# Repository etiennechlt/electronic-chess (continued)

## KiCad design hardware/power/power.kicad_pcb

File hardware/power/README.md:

# Carte puissance : pack 3S, charge, protection, jauge

Générée par `tools/boardgen` (module `power`). 100 x 60 mm, 2 couches,
plan de masse en face arrière. Elle gère trois cellules plates 1S 5 Ah.

- **Entrée** : 20 V depuis un module déclencheur USB-C PD du commerce
  (connecteur JST XH 2 broches), TVS SMBJ24A, sens de courant d'entrée
  10 mohms, deux P-FET AO3401A dos à dos (drain commun) que la sortie
  ACDRV, active bas, pilote.
- **Chargeur** : BQ24610, buck synchrone à deux AO3400A, self 10 µH,
  sens de courant 50 mohms (1 A = 50 mV), régulation 12,6 V par
  diviseur sur VFB, courant de charge 1 A (ISET1 à 0,995 V), précharge
  et fin de charge 0,2 A (ISET2 à 0,101 V), limite d'entrée 2,5 A
  (ACSET à 0,499 V), fenêtre de température 0 à 45 °C par le réseau
  5,23 k / 30,1 k de la fiche sur une CTN 10 k, sorties STAT et PG
  tirées au 3,3 V de l'AFE. Pas de chemin d'alimentation : le système
  tourne sur le pack, BATDRV reste libre.
- **Protection** : BQ76920 (AFE 3 à 5S) avec ses filtres 1 k / 100 nF
  par cellule, deux FET AO3400A en bas côté dans le retour du pack (DSG
  source côté cellules après la résistance de mesure, CHG source sur
  PACK-), sens 5 mohms, CTN, I2C vers le cerveau, sortie ALERT.
- **Jauge** : INA219 sur un shunt 10 mohms côté haut, même bus I2C.
- **Sorties** : fusible 2 A, embase pour un interrupteur, bouton de
  réveil (PWR_KEY), liaison 2 x 4 vers le cerveau, connecteur cellules
  JST XH 4 broches (B-, B1, B2, B+).

Les valeurs d'ISET, d'ACSET et du diviseur de tension suivent
l'application type du BQ24610, revues dans la
[note 14](../../docs/notes/14-revue-des-cartes.md) ; les formules
(ICHG = V(ISET1) / 20 RSR, IPRE = ITERM = V(ISET2) / 10 RSR) et la
plage admise de V(ISET2) restent à confirmer sur la fiche. Points
ouverts : la CTN de charge est sur la carte alors que le yaml la veut
sur le pack (deux broches de plus au connecteur cellules), et le cerveau
ne doit jamais ouvrir DSG par I2C (rien ne le refermerait).

```bash
PYTHONPATH=tools .venv/bin/python -m boardgen build power --render docs/images/power.png
```

## Résultat du build

Généré par `python -m boardgen build power` :

| Composants | Segments | Vias | Nets fermés | Nets ouverts | Défauts d'isolement |
|---|---|---|---|---|---|
| 82 | 429 | 158 | 42 | 10 | 0 |

Nets à finir dans pcbnew (le routeur les a laissés ouverts) :
- REGN: 2 pad(s) left open (usable start cells 28, goal cells 72)
- TS1: 2 pad(s) left open (usable start cells 43, goal cells 63)
- SCL: 4 pad(s) left open (usable start cells 34, goal cells 314)
- SDA: 4 pad(s) left open (usable start cells 34, goal cells 318)
- 3V3_BMS: 1 pad(s) left open (usable start cells 534, goal cells 34)
- SRN: 1 pad(s) left open (usable start cells 163, goal cells 84)
- SRP: 1 pad(s) left open (usable start cells 642, goal cells 84)
- CELL3: 6 pad(s) left open (usable start cells 30, goal cells 483)
- PACK+: 1 pad(s) left open (usable start cells 313, goal cells 100)
- BAT-: 16 pad(s) left open (usable start cells 39, goal cells 969)

DRC KiCad 7 (`tools/drc.py`, zones remplies) : 307 signalements, 69 éléments non connectés (les nets ouverts ci-dessus), erreurs restantes : aucune ; avertissements sans effet sur la fabrication : silk_overlap 121, lib_footprint_issues 82, via_dangling 56, silk_over_copper 36, track_dangling 12. Le contrôle d'isolement exact du générateur ne signale aucun défaut. Les vias d'éventail des boîtiers fins font 0,45 mm (perçage 0,2 mm), dans les capacités standard de JLCPCB, à confirmer sur le devis.

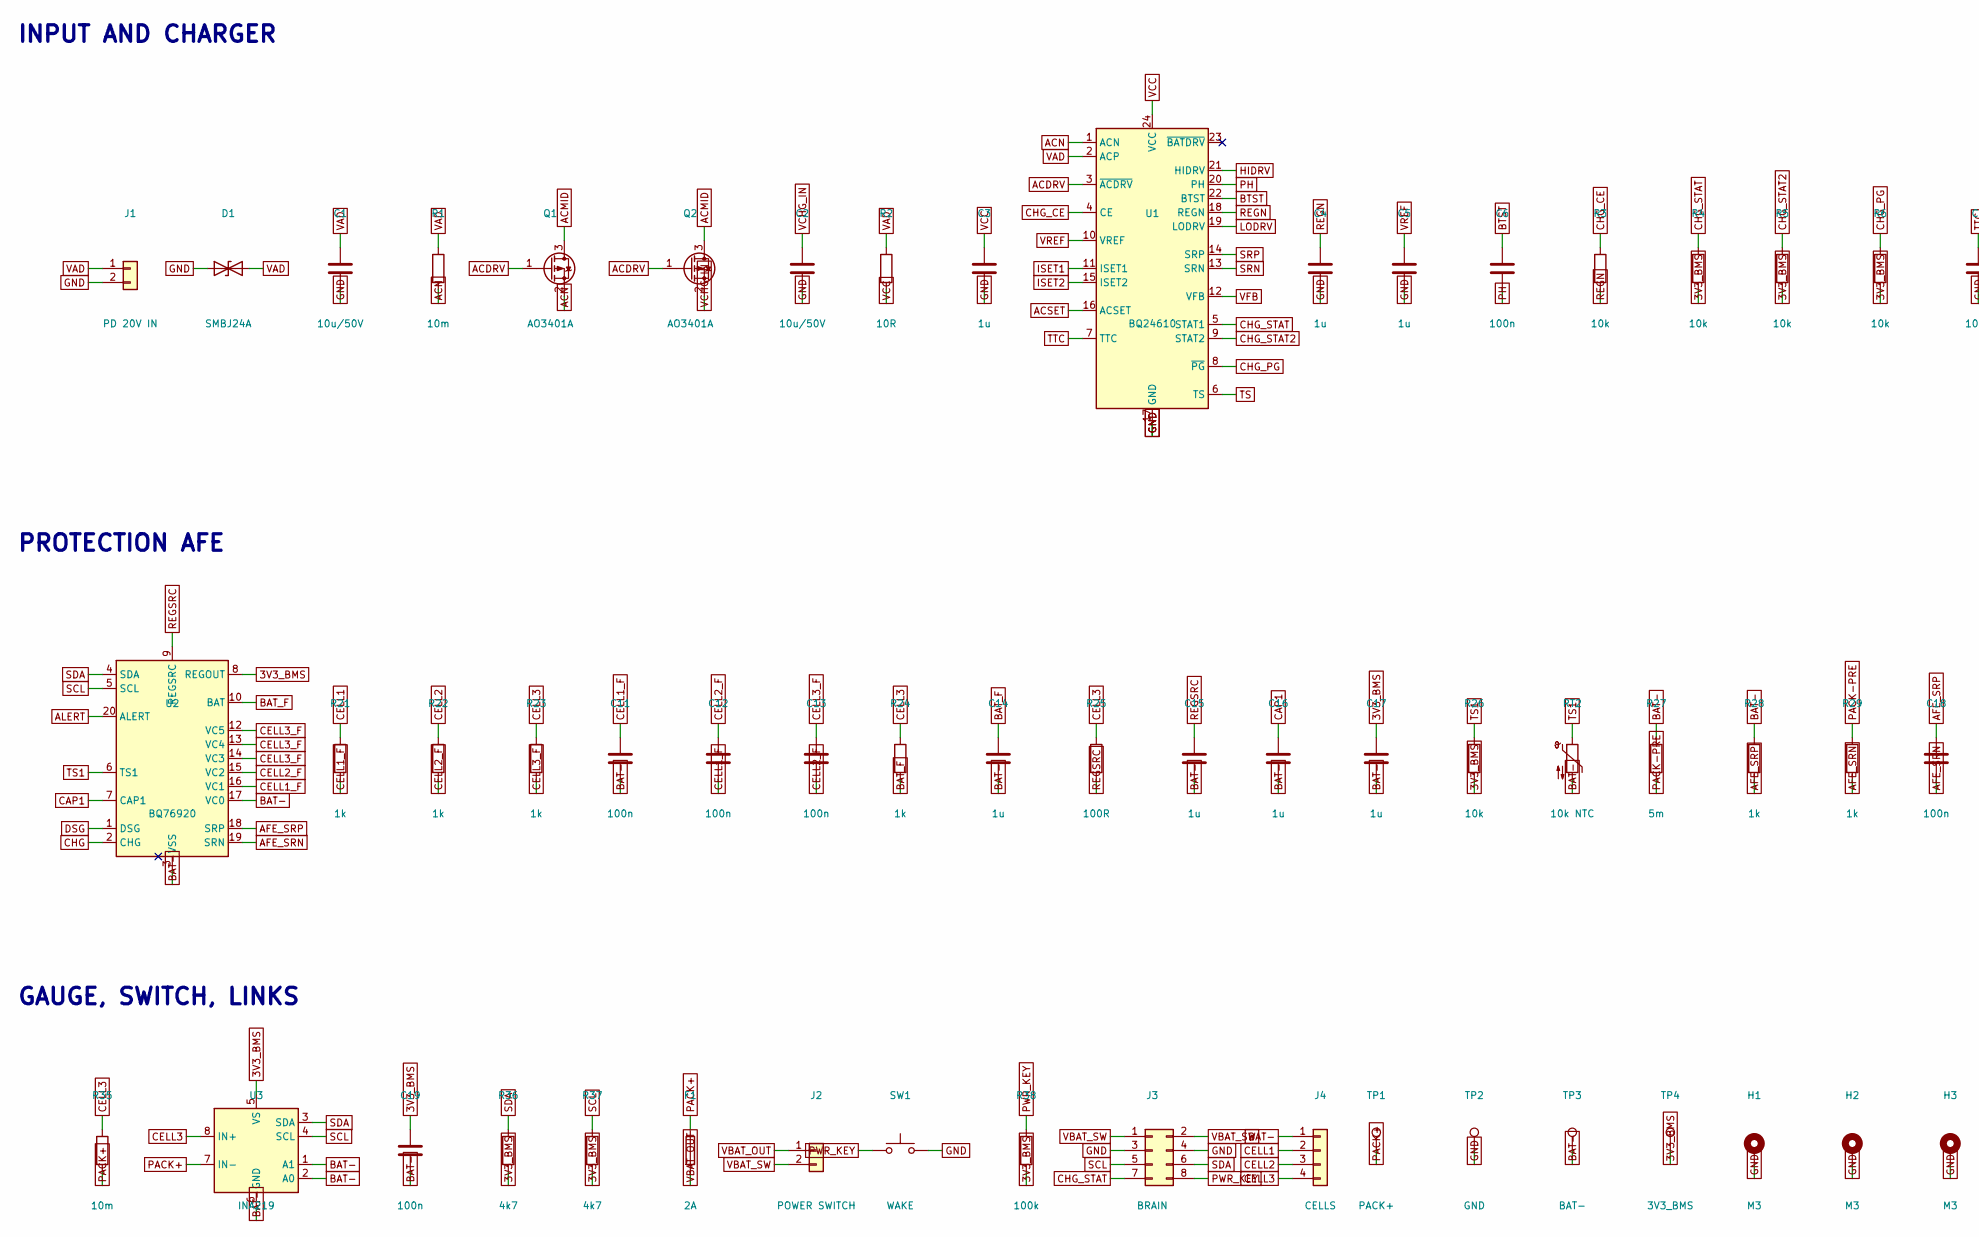
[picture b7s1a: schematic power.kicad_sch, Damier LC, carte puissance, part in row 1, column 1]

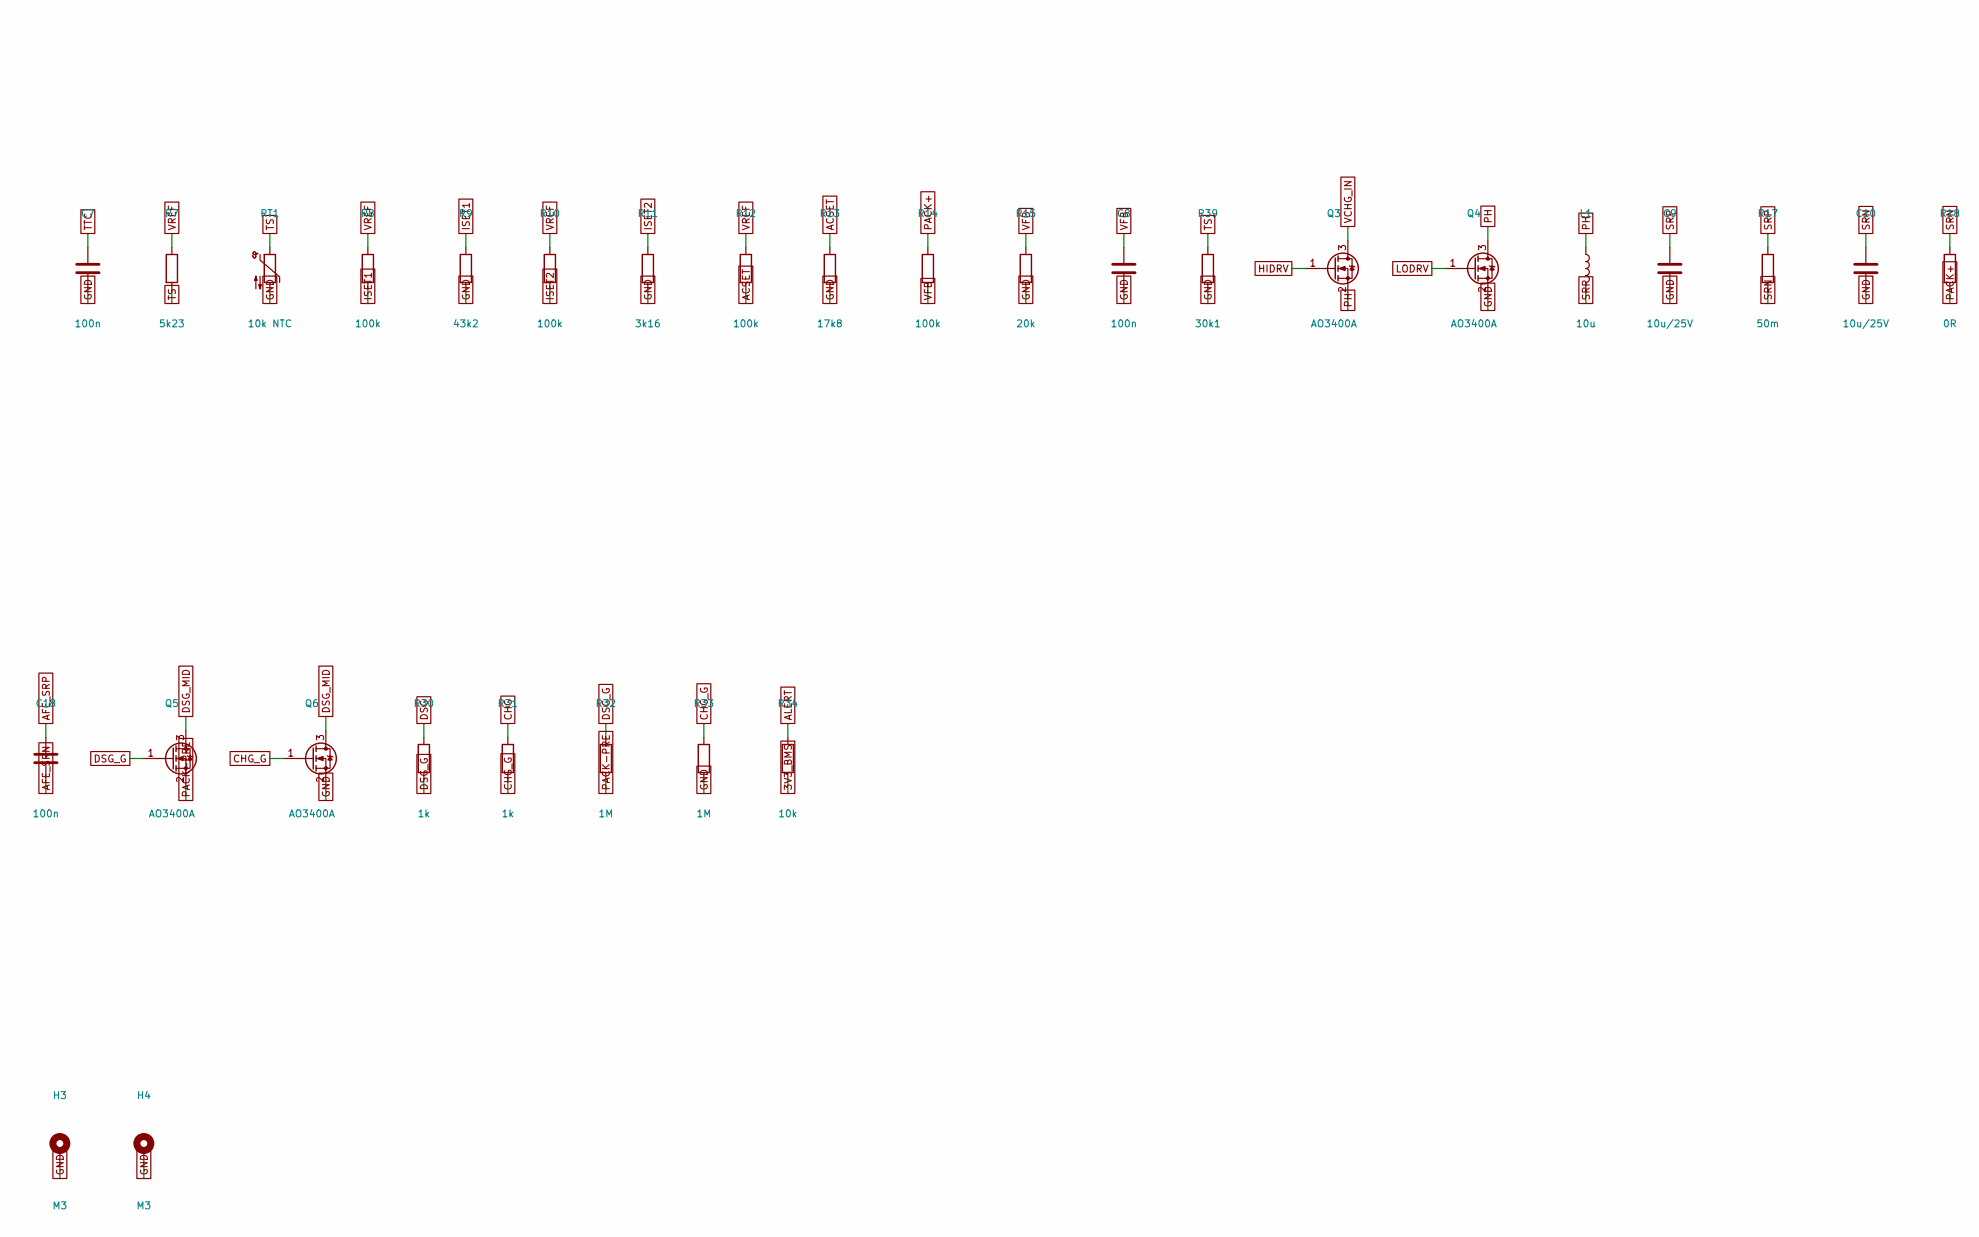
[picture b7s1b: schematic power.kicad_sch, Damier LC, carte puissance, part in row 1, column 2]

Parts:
C1, C2: 10u/50V; C_1206_3216Metric
C3, C4, C5, C14, C15, C16, C17: 1u; C_0603_1608Metric
C6, C7, C8, C11, C12, C13, C18, C19: 100n; C_0603_1608Metric
C9, C10: 10u/25V; C_1206_3216Metric
D1: SMBJ24A; D_SMB; MPN SMBJ24A; LCSC C113966
F1: 2A; Fuse_1206_3216Metric
H1, H2, H3, H4: M3; MountingHole_3.2mm_M3_Pad
J1: PD 20V IN; JST_XH_B2B-XH-A_1x02_P2.50mm_Vertical
J2: POWER SWITCH; JST_XH_B2B-XH-A_1x02_P2.50mm_Vertical
J3: BRAIN; PinHeader_2x04_P2.54mm_Vertical
J4: CELLS; JST_XH_B4B-XH-A_1x04_P2.50mm_Vertical
L1: 10u; L_Bourns_SRN6045TA; MPN SRN6045TA-100M; LCSC C167222
Q1, Q2: AO3401A; SOT-23; MPN AO3401A; LCSC C15127
Q3, Q4, Q5, Q6: AO3400A; SOT-23; MPN AO3400A; LCSC C20917
R1, R35: 10m; R_1206_3216Metric
R2: 10R; R_0603_1608Metric
R3, R4, R5, R6, R26, R34: 10k; R_0603_1608Metric
R7: 5k23; R_0603_1608Metric
R8, R10, R12, R14, R38: 100k; R_0603_1608Metric
R9: 43k2; R_0603_1608Metric
R11: 3k16; R_0603_1608Metric
R13: 17k8; R_0603_1608Metric
R15: 20k; R_0603_1608Metric
R17: 50m; R_1206_3216Metric
R18: 0R; R_0603_1608Metric
R21, R22, R23, R24, R28, R29, R30, R31: 1k; R_0603_1608Metric
R25: 100R; R_0603_1608Metric
R27: 5m; R_1206_3216Metric
R32, R33: 1M; R_0603_1608Metric
R36, R37: 4k7; R_0603_1608Metric
R39: 30k1; R_0603_1608Metric
RT1, RT2: 10k NTC; R_0603_1608Metric; MPN NCP18XH103F03RB
SW1: WAKE; SW_SPST_PTS645; MPN PTS645SM43SMTR92; LCSC C221929
TP1: PACK+; TestPoint_Pad_1.5x1.5mm
TP2: GND; TestPoint_Pad_1.5x1.5mm
TP3: BAT-; TestPoint_Pad_1.5x1.5mm
TP4: 3V3_BMS; TestPoint_Pad_1.5x1.5mm
U1: BQ24610; QFN-24-1EP_4x4mm_P0.5mm_EP2.7x2.7mm; MPN BQ24610RGER; LCSC C130050
U2: BQ76920; TSSOP-20_4.4x6.5mm_P0.65mm; MPN BQ76920PWR; LCSC C130052
U3: INA219; SOIC-8_3.9x4.9mm_P1.27mm; MPN INA219BIDR; LCSC C138092

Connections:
3V3_BMS: C17.1, C19.1, R4.2, R5.2, R6.2, R26.2, R34.2, R36.2, R37.2, R38.2, TP4.1, U2.8 (REGOUT), U3.5 (VS)
ACDRV: Q1.1 (G), Q2.1 (G), U1.3 (~ACDRV)
ACMID: Q1.3 (D), Q2.3 (D)
ACN: Q1.2 (S), R1.2, U1.1 (ACN)
ACSET: R12.2, R13.1, U1.16 (ACSET)
AFE_SRN: C18.2, R29.2, U2.19 (SRN)
AFE_SRP: C18.1, R28.2, U2.18 (SRP)
ALERT: R34.1, U2.20 (ALERT)
BAT-: C11.2, C14.2, C15.2, C16.2, C17.2, C19.2, J4.1, R27.1, R28.1, RT2.2, TP3.1, U2.3 (VSS), U2.17 (VC0), U3.1 (A1), U3.2 (A0), U3.6 (GND)
BAT_F: C14.1, R24.2, U2.10 (BAT)
BTST: C6.1, U1.22 (BTST)
CAP1: C16.1, U2.7 (CAP1)
CELL1: J4.2, R21.1
CELL1_F: C11.1, C12.2, R21.2, U2.16 (VC1)
CELL2: J4.3, R22.1
CELL2_F: C12.1, C13.2, R22.2, U2.15 (VC2)
CELL3: J4.4, R23.1, R24.1, R25.1, R35.1, U3.8 (IN+)
CELL3_F: C13.1, R23.2, U2.12 (VC5), U2.13 (VC4), U2.14 (VC3)
CHG: R31.1, U2.2 (CHG)
CHG_CE: R3.1, U1.4 (CE)
CHG_G: Q6.1 (G), R31.2, R33.1
CHG_PG: R6.1, U1.8 (~PG)
CHG_STAT: J3.7, R4.1, U1.5 (STAT1)
CHG_STAT2: R5.1, U1.9 (STAT2)
DSG: R30.1, U2.1 (DSG)
DSG_G: Q5.1 (G), R30.2, R32.1
DSG_MID: Q5.3 (D), Q6.3 (D)
GND: C1.2, C2.2, C3.2, C4.2, C5.2, C7.2, C8.2, C9.2, C10.2, D1.1 (A1), H1.1, H2.1, H3.1, H4.1, J1.2, J3.3, J3.4, Q4.2 (S), Q6.2 (S), R9.2, R11.2, R13.2, R15.2, R33.2, R39.2, RT1.2, SW1.2, TP2.1, U1.17 (GND), U1.25 (GND)
HIDRV: Q3.1 (G), U1.21 (HIDRV)
ISET1: R8.2, R9.1, U1.11 (ISET1)
ISET2: R10.2, R11.1, U1.15 (ISET2)
LODRV: Q4.1 (G), U1.19 (LODRV)
PACK+: F1.1, R14.1, R18.2, R35.2, TP1.1, U3.7 (IN-)
PACK-PRE: Q5.2 (S), R27.2, R29.1, R32.2
PH: C6.2, L1.1, Q3.2 (S), Q4.3 (D), U1.20 (PH)
PWR_KEY: J3.8, R38.1, SW1.1
REGN: C4.1, R3.2, U1.18 (REGN)
REGSRC: C15.1, R25.2, U2.9 (REGSRC)
SCL: J3.5, R37.1, U2.5 (SCL), U3.4 (SCL)
SDA: J3.6, R36.1, U2.4 (SDA), U3.3 (SDA)
SRN: C10.1, R17.2, R18.1, U1.13 (SRN)
SRP: C9.1, L1.2, R17.1, U1.14 (SRP)
TS: R7.2, R39.1, RT1.1, U1.6 (TS)
TS1: R26.1, RT2.1, U2.6 (TS1)
TTC: C7.1, U1.7 (TTC)
VAD: C1.1, D1.2 (A2), J1.1, R1.1, R2.1, U1.2 (ACP)
VBAT_OUT: F1.2, J2.1
VBAT_SW: J2.2, J3.1, J3.2
VCC: C3.1, R2.2, U1.24 (VCC)
VCHG_IN: C2.1, Q2.2 (S), Q3.3 (D)
VFB: C8.1, R14.2, R15.1, U1.12 (VFB)
VREF: C5.1, R7.1, R8.1, R10.1, R12.1, U1.10 (VREF)

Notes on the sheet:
INPUT AND CHARGER
PROTECTION AFE
GAUGE, SWITCH, LINKS

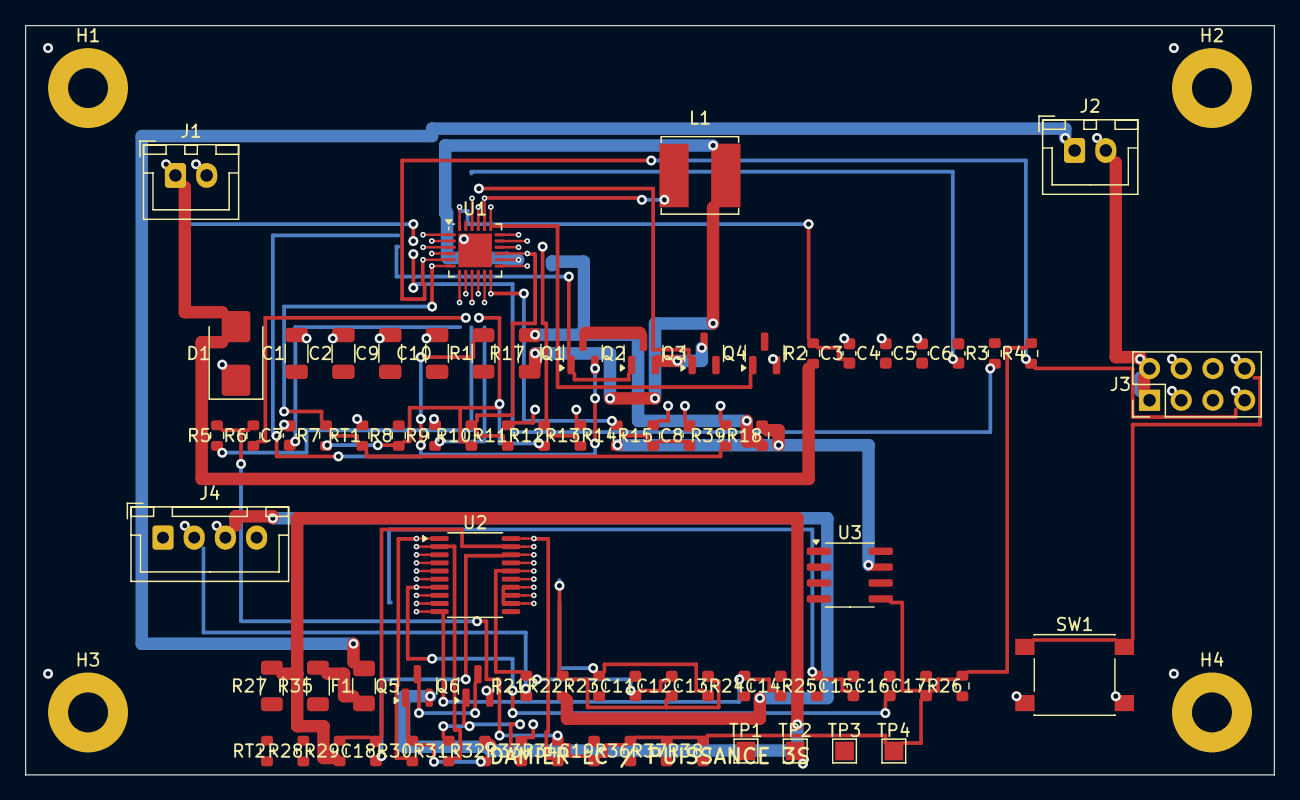
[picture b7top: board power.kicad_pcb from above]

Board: 2 copper layers, 100.0 x 60.0 mm, 82 parts (0 on the bottom side), 52 nets.

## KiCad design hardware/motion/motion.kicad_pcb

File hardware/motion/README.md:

# Carte moteurs : option chariot

Générée par `tools/boardgen` (module `motion`). 90 x 60 mm, 2 couches.
Elle vit dans la base chariot et se branche au cerveau par la nappe
IDC 2 x 10.

- Deux embases pour modules TMC2209 SilentStepStick (brochage Pololu :
  EN, MS1, MS2, PDN_UART x 2, CLK, STEP, DIR ; VM, GND, 2B, 2A, 1A, 1B,
  VIO, GND), adresses UART 0 et 1 par MS1, un seul fil UART à travers
  1 k, réserve 100 µF par pilote.
- Moteurs sur JST XH 4 broches, fins de course X et Y sur JST XH 3
  broches (GND, 3,3 V, signal), servo de l'actionneur d'aimant sur
  JST XH 3 broches (signal, 5 V, GND).
- Points de test, quatre trous M3.

```bash
PYTHONPATH=tools .venv/bin/python -m boardgen build motion --render docs/images/motion.png
```

## Résultat du build

Généré par `python -m boardgen build motion` :

| Composants | Segments | Vias | Nets fermés | Nets ouverts | Défauts d'isolement |
|---|---|---|---|---|---|
| 31 | 151 | 109 | 27 | 1 | 0 |

Nets à finir dans pcbnew (le routeur les a laissés ouverts) :
- MOT_DIAG

Le contrôle d'isolement exact ne signale aucun défaut : ce qui est
tracé respecte les règles, ce qui manque est listé ci-dessus. Les vias
d'éventail des boîtiers fins font 0,45 mm (perçage 0,2 mm), à
confirmer avec le fabricant avant commande.

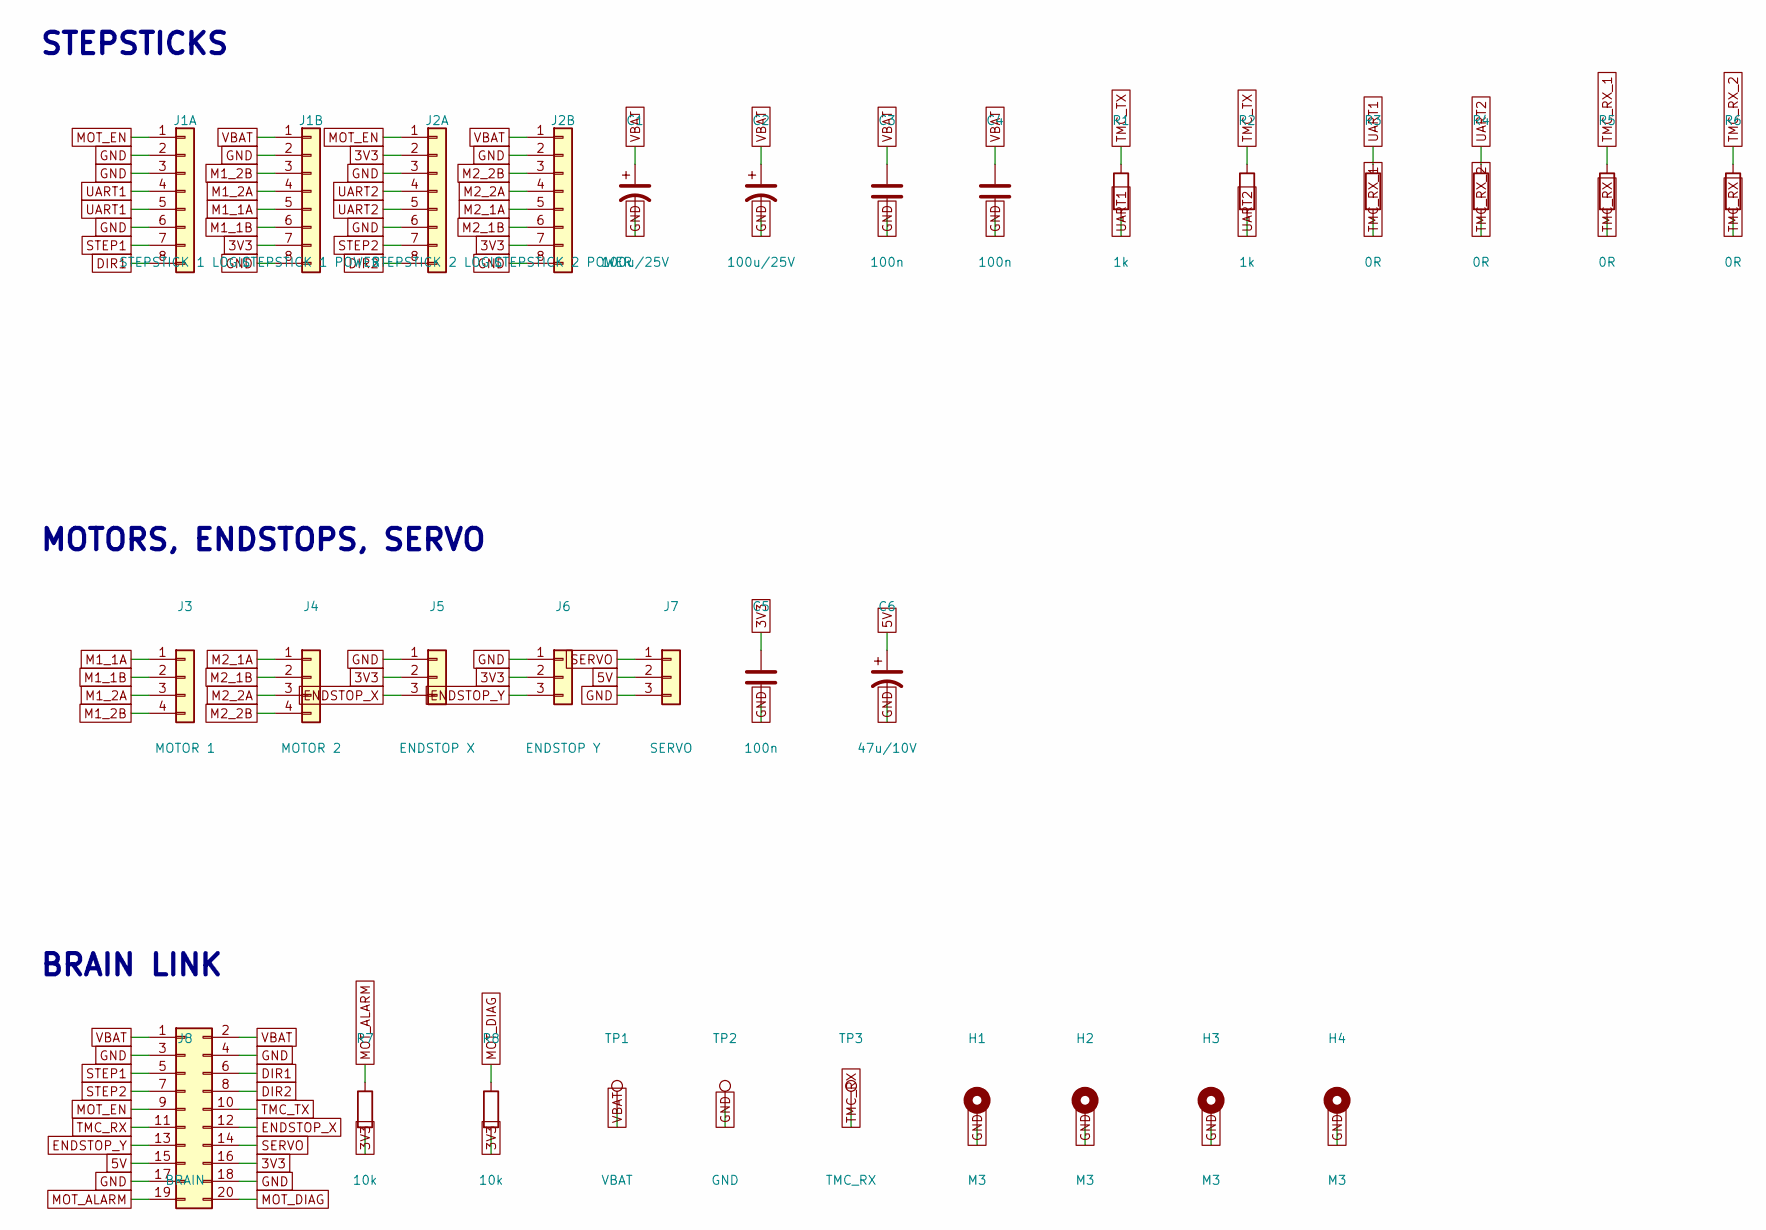
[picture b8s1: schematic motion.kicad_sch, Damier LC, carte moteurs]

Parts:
C1, C2: 100u/25V; CP_Elec_8x10.5
C3, C4, C5: 100n; C_0603_1608Metric
C6: 47u/10V; CP_Elec_6.3x7.7
H1, H2, H3, H4: M3; MountingHole_3.2mm_M3_Pad
J1A: STEPSTICK 1 LOGIC; PinHeader_1x08_P2.54mm_Vertical
J1B: STEPSTICK 1 POWER; PinHeader_1x08_P2.54mm_Vertical
J2A: STEPSTICK 2 LOGIC; PinHeader_1x08_P2.54mm_Vertical
J2B: STEPSTICK 2 POWER; PinHeader_1x08_P2.54mm_Vertical
J3: MOTOR 1; JST_XH_B4B-XH-A_1x04_P2.50mm_Vertical
J4: MOTOR 2; JST_XH_B4B-XH-A_1x04_P2.50mm_Vertical
J5: ENDSTOP X; JST_XH_B3B-XH-A_1x03_P2.50mm_Vertical
J6: ENDSTOP Y; JST_XH_B3B-XH-A_1x03_P2.50mm_Vertical
J7: SERVO; JST_XH_B3B-XH-A_1x03_P2.50mm_Vertical
J8: BRAIN; PinHeader_2x10_P2.54mm_Vertical
R1, R2: 1k; R_0603_1608Metric
R3, R4, R5, R6: 0R; R_0603_1608Metric
R7, R8: 10k; R_0603_1608Metric
TP1: VBAT; TestPoint_Pad_1.5x1.5mm
TP2: GND; TestPoint_Pad_1.5x1.5mm
TP3: TMC_RX; TestPoint_Pad_1.5x1.5mm

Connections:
3V3: C5.1, J1B.7, J2A.2, J2B.7, J5.2, J6.2, J8.16, R7.2, R8.2
5V: C6.1, J7.2, J8.15
DIR1: J1A.8, J8.6
DIR2: J2A.8, J8.8
ENDSTOP_X: J5.3, J8.12
ENDSTOP_Y: J6.3, J8.13
GND: C1.2, C2.2, C3.2, C4.2, C5.2, C6.2, H1.1, H2.1, H3.1, H4.1, J1A.2, J1A.3, J1A.6, J1B.2, J1B.8, J2A.3, J2A.6, J2B.2, J2B.8, J5.1, J6.1, J7.3, J8.3, J8.4, J8.17, J8.18, TP2.1
M1_1A: J1B.5, J3.1
M1_1B: J1B.6, J3.2
M1_2A: J1B.4, J3.3
M1_2B: J1B.3, J3.4
M2_1A: J2B.5, J4.1
M2_1B: J2B.6, J4.2
M2_2A: J2B.4, J4.3
M2_2B: J2B.3, J4.4
MOT_ALARM: J8.19, R7.1
MOT_DIAG: J8.20, R8.1
MOT_EN: J1A.1, J2A.1, J8.9
SERVO: J7.1, J8.14
STEP1: J1A.7, J8.5
STEP2: J2A.7, J8.7
TMC_RX: J8.11, R5.2, R6.2, TP3.1
TMC_RX_1: R3.2, R5.1
TMC_RX_2: R4.2, R6.1
TMC_TX: J8.10, R1.1, R2.1
UART1: J1A.4, J1A.5, R1.2, R3.1
UART2: J2A.4, J2A.5, R2.2, R4.1
VBAT: C1.1, C2.1, C3.1, C4.1, J1B.1, J2B.1, J8.1, J8.2, TP1.1

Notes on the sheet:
STEPSTICKS
MOTORS, ENDSTOPS, SERVO
BRAIN LINK

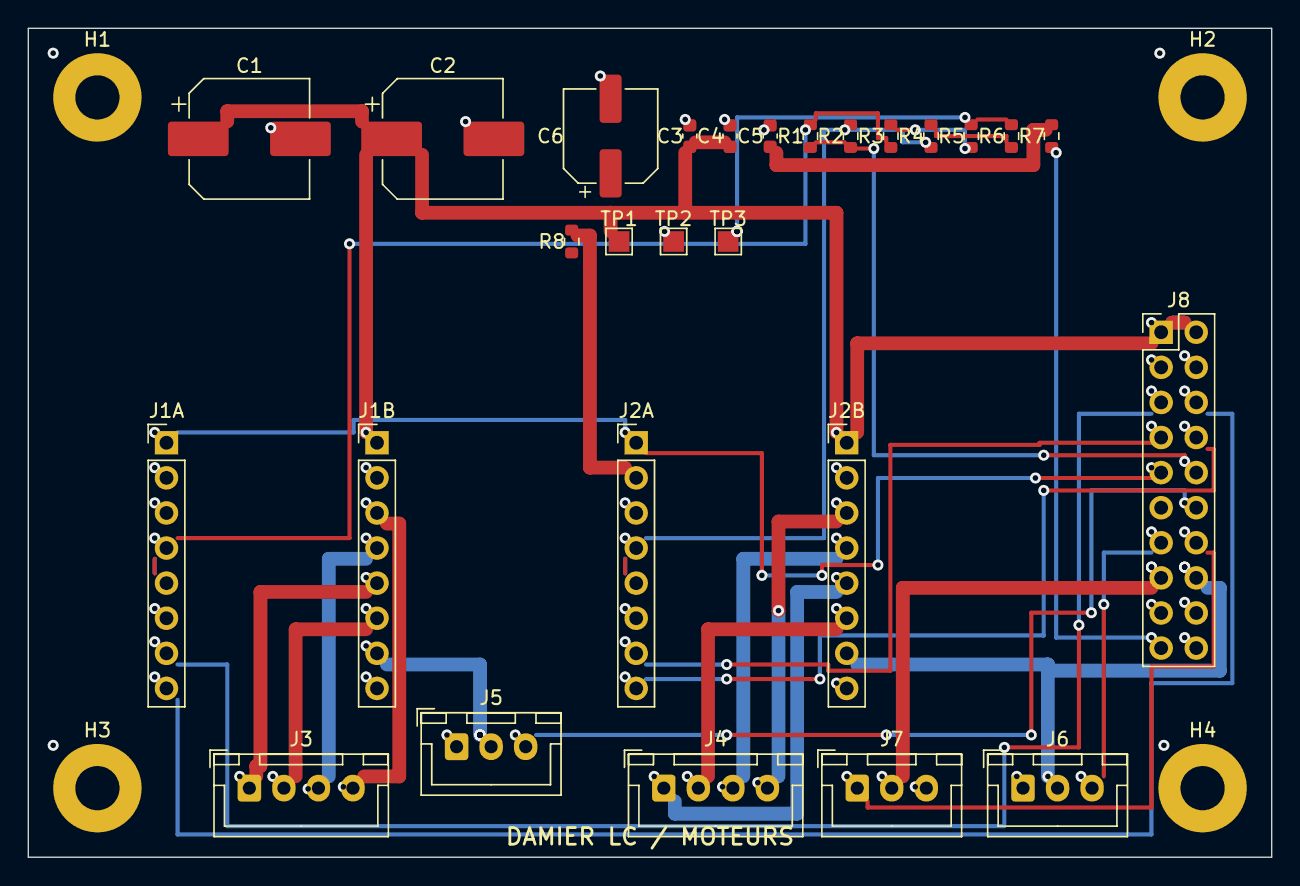
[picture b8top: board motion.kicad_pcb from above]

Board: 2 copper layers, 90.0 x 60.0 mm, 31 parts (0 on the bottom side), 28 nets.

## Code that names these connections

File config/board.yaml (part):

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
bench:                         # the Nucleo bench of note 19: NUCLEO=1 build of firmware/board
  board: "Nucleo-G474RE"       # and the bench shield of boardgen (module bench)
  console: { usart: 2, tx: PA2, rx: PA3 }   # ST-Link virtual COM port (UM2505), 115200 bauds
  arduino_pins:                # Arduino Uno V3 connectors of the Nucleo-64 (UM2505)
    A0: PA0
    A1: PA1
    A2: PA4
    A3: PB0
    A4: PC1
    A5: PC0
    D0: PC5
    D1: PC4
    D2: PA10
    D3: PB3
    D4: PB5
    D5: PB4
    D6: PB10
    D7: PA8
    D8: PA9
    D9: PC7
    D10: PB6
    D11: PA7
    D12: PA6
    D13: PA5
    D14: PB9
    D15: PB8
  # Quadrant bus on those connectors, keyed like plateau.brain.mcu_pins.
  # Every signal sits on the brain's own pin (tests/test_bench.py) except
  # DAMP_EN_N: PC2 only reaches a Morpho connector, so the bench moves it
  # to D6 and the shield needs no Morpho socket; board.h applies the move.
  signals:
    ADC1: A0
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    pi_header: { pins: 4, rail: buck_5v }
  uart_isolator: { part: ADuM1201ARZ, bypass_jumpers: true }
  nucleo_pins:                   # Nucleo-G474RE Arduino connector mapping
    amp_out: { arduino: A0, mcu: PA0 }    # ADC1_IN1
    comp_in: { arduino: A1, mcu: PA1 }    # COMP1_INP
    pulse_en: { arduino: A2, mcu: PA4 }
    mux_a0: { arduino: D3, mcu: PB3 }
    mux_a1: { arduino: D4, mcu: PB5 }
    mux_inh: { arduino: D5, mcu: PB4 }  # 4052 Inh, active high
    damp_1: { arduino: D6, mcu: PB10 }
    damp_2: { arduino: D7, mcu: PA8 }
    damp_3: { arduino: D9, mcu: PC7 }
    damp_4: { arduino: D10, mcu: PB6 }
    drive_1: { arduino: D11, mcu: PA7 }
    drive_2: { arduino: D12, mcu: PA6 }
    drive_3: { arduino: D14, mcu: PB9 }
    drive_4: { arduino: D15, mcu: PB8 }
    led_din: { arduino: D13, mcu: PA5 }   # TIM2_CH1, WS2812 via PWM DMA
    pi_uart_tx: { arduino: D8, mcu: PA9 }   # USART1, through the isolator
    pi_uart_rx: { arduino: D2, mcu: PA10 }
    # CSV output uses the Nucleo virtual COM port (USART2 PA2/PA3)

plateau:                       # 8x8 board built directly from 4x4 quadrants (ADR 0010)
  grid: 8
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      pins: 16
      # GND, 5V_LED, LED_DIN and LED_DOUT get a dedicated fan-out on the
      # quadrant (bus ties, LED chain): keep them apart, never on adjacent pins
      pinout: [GND, 5VA, GND, AMP_OUT, 3V3, MUX_A0, LED_DIN, MUX_A1,
               MUX_A2, 5V_LED, MUX_EN_L, MUX_EN_H, LED_DOUT, PULSE_EN,
               DAMP_EN_N, VIN]
    routing:                   # quadgen numbers
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      cell_entry_x_mm: 3.8     # A on F.Cu at y - 0.6, B on B.Cu at y + 0.6
    front_end:
      drive_decoder: 74HC4514  # 4 to 16, active high: coil excitation gates, inhibited by PULSE_EN_N
      damp_decoder: 74HC154    # 4 to 16, active low: P-FET damping gates, enabled by DAMP_EN_N
      flyback_diode: "SS34FL, SOD-123FL, 1 mm de haut"
      logic_rail: 3V3          # decoders and inverter; mux, INA and op amps on 5VA
    mounting_hole_d_mm: 3.2
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    board_mm: [120.0, 80.0]
    layers: 4
    mcu_pins:                  # STM32G474RE, to validate against the datasheet before fab
      ADC1: PA0                # quadrant 1, ADC1_IN1
      ADC2: PA6                # quadrant 2, ADC2_IN3
      ADC3: PB0                # quadrant 3, ADC3_IN12
      ADC4: PB14               # quadrant 4, ADC4_IN4
      LED_DIN_MCU: PA5         # TIM2_CH1, WS2812 chain through the 74AHCT1G125
      MUX_A0: PB3
      MUX_A1: PB5
      MUX_A2: PB4
      MUX_EN_L: PC0
      MUX_EN_H: PC1
      PULSE_EN: PA4
      DAMP_EN_N: PC2
      STEP1: PC6               # TIM3_CH1
      DIR1: PC7
      STEP2: PC8               # TIM3_CH3
      DIR2: PC9
      MOT_EN: PC12
      TMC_TX: PC10             # USART3
      TMC_RX: PC11
      ENDSTOP_X: PD2
      ENDSTOP_Y: PA3
      SERVO: PB6               # TIM4_CH1
      I2C_SCL: PA15            # I2C1, power board AFE and gauge (PB8 is BOOT0)
      I2C_SDA: PB7
      BUZZER: PB10             # TIM2_CH3
      LED_STAT1: PC13
      LED_STAT2: PC14
      LED_STAT3: PC15
      LED_STAT4: PA8
      USER_BTN: PB11
      COMM_EN: PB15            # comms module load switch
      MCU_TX: PA9              # USART1 to the isolated UART
      MCU_RX: PA10
      USB_DM_MCU: PA11
      USB_DP_MCU: PA12
      SWDIO: PA13
      SWCLK: PA14
      CHG_STAT: PA7
      PWR_KEY: PB1
      MOT_ALARM: PB2
      MOT_DIAG: PC4
      ESP_EN: PB12
      ESP_IO0: PB13

clock:                         # separate rocker chess clock, BLE to the board (ADR 0010)
  radio: ble
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      cluster: [4, 5, 6, 7]
      ground: 8                # zero of the path
      rail_half: 9             # switched row-1 rail divided by two
      led_step: 10             # LED pin through a divider by two and a known RC
      extension: [11, 12, 13, 14, 15]
    esp32:
      module: ESP32-S3-WROOM-1-N8   # D2: placed by JLCPCB, Standard PCBA only
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      usb_gpios: [19, 20]
      psram_gpios: [35, 36, 37]         # left free for an R8 module
      analog_signals: [MUX_OUT, HALL_A1, HALL_B1, HALL_A2, HALL_B2, PICKUP]   # on ADC1
      usb_signals: [USB_DM, USB_DP]     # the only signals allowed on usb_gpios, in order
      pins:
        MUX_OUT: 1
        HALL_A1: 2
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      cluster: [4, 5, 6, 7]    # the four sensors around the centre of A1
      ground: 8                # zero of the path
      rail_half: 9             # switched sensor rail divided by two
      led_step: 10             # LED pin through a divider by two and a known RC
      extension: [11, 12, 13, 14, 15]   # header: outside probes
      grounded: [2, 3]         # unused inputs, tied to ground, never floating
    esp32:                     # module, GPIO lists and rules in mockup.esp32
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
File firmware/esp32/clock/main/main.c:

/* Rocker chess clock: two microswitches under the bar, an encoder for
 * the menus, a buzzer, a 2.4 inch SPI display and a BLE link to the
 * board's bridge (Nordic UART Service, central role). Pins follow
 * tools/boardgen/clock.py (ESP_PINS). Not compiled in CI, see
 * ../README.md. */
#include <stdio.h>
#include <string.h>

#include "chessclock.h"
#include "driver/gpio.h"
#include "driver/ledc.h"
#include "esp_log.h"
#include "esp_timer.h"
#include "freertos/FreeRTOS.h"
#include "freertos/queue.h"
#include "freertos/task.h"
#include "nus.h"
#include "proto.h"
#include "ui.h"

#define PIN_SW_WHITE 12
#define PIN_SW_BLACK 13
#define PIN_ENC_A 9
#define PIN_ENC_B 10
#define PIN_ENC_SW 11
#define PIN_BUZZER 14

static const char *TAG = "clock";

typedef enum { EV_WHITE, EV_BLACK, EV_ENC_CW, EV_ENC_CCW, EV_ENC_PUSH } event_t;

static QueueHandle_t events;
static chessclock_t clk;
static proto_reader_t from_board;

/* presets shown in the menu: base seconds, increment seconds, mode */
static const struct { uint32_t base_s, inc_s; clock_mode_t mode; const char *label; } PRESETS[] = {
    {180, 2, MODE_FISCHER, "3+2"},   {300, 0, MODE_SIMPLE, "5+0"},
    {600, 0, MODE_SIMPLE, "10+0"},   {900, 10, MODE_FISCHER, "15+10"},
    {1800, 0, MODE_SIMPLE, "30+0"},  {5400, 30, MODE_FISCHER, "90+30"},
    {0, 0, MODE_FREE, "libre"},
};
static int preset = 3;

static uint32_t now_ms(void) { return (uint32_t)(esp_timer_get_time() / 1000); }

/* ------------------------------------------------------------- inputs */

static void IRAM_ATTR on_gpio(void *arg) {
    event_t ev = (event_t)(intptr_t)arg;
    BaseType_t woken = pdFALSE;
    xQueueSendFromISR(events, &ev, &woken);
    if (woken) {
        portYIELD_FROM_ISR();
    }
}

static void IRAM_ATTR on_encoder(void *arg) {
    (void)arg;
    /* half-step decoding on the A edge: direction from B */
    event_t ev = gpio_get_level(PIN_ENC_B) ? EV_ENC_CW : EV_ENC_CCW;
    BaseType_t woken = pdFALSE;
    xQueueSendFromISR(events, &ev, &woken);
    if (woken) {
        portYIELD_FROM_ISR();
    }
}

static void inputs_init(void) {
    gpio_config_t in = {
        .pin_bit_mask = (1ull << PIN_SW_WHITE) | (1ull << PIN_SW_BLACK) | (1ull << PIN_ENC_A) |
                        (1ull << PIN_ENC_B) | (1ull << PIN_ENC_SW),
        .mode = GPIO_MODE_INPUT,
        .pull_up_en = GPIO_PULLUP_ENABLE,
        .intr_type = GPIO_INTR_NEGEDGE,
    };
    gpio_config(&in);
    gpio_set_intr_type(PIN_ENC_B, GPIO_INTR_DISABLE);
    gpio_install_isr_service(0);
    gpio_isr_handler_add(PIN_SW_WHITE, on_gpio, (void *)EV_WHITE);
    gpio_isr_handler_add(PIN_SW_BLACK, on_gpio, (void *)EV_BLACK);
    gpio_isr_handler_add(PIN_ENC_SW, on_gpio, (void *)EV_ENC_PUSH);
    gpio_isr_handler_add(PIN_ENC_A, on_encoder, NULL);
}

/* ------------------------------------------------------------- buzzer */

static void buzzer_init(void) {
    ledc_timer_config_t t = {
        .speed_mode = LEDC_LOW_SPEED_MODE, .duty_resolution = LEDC_TIMER_10_BIT,
        .timer_num = LEDC_TIMER_0, .freq_hz = 2700, .clk_cfg = LEDC_AUTO_CLK,
    };
    ledc_timer_config(&t);
    ledc_channel_config_t ch = {
        .gpio_num = PIN_BUZZER, .speed_mode = LEDC_LOW_SPEED_MODE, .channel = LEDC_CHANNEL_0,
        .timer_sel = LEDC_TIMER_0, .duty = 0, .hpoint = 0,
    };
    ledc_channel_config(&ch);
}

static void beep(int times) {
    for (int i = 0; i < times; i++) {
        ledc_set_duty(LEDC_LOW_SPEED_MODE, LEDC_CHANNEL_0, 512);
        ledc_update_duty(LEDC_LOW_SPEED_MODE, LEDC_CHANNEL_0);
        vTaskDelay(pdMS_TO_TICKS(120));
        ledc_set_duty(LEDC_LOW_SPEED_MODE, LEDC_CHANNEL_0, 0);
        ledc_update_duty(LEDC_LOW_SPEED_MODE, LEDC_CHANNEL_0);
        vTaskDelay(pdMS_TO_TICKS(80));
    }
}

/* --------------------------------------------------------------- link */

static void send_times(void) {
    char line[48];
    snprintf(line, sizeof line, "C,%ld,%ld,%c\n", (long)clk.left_ms[0], (long)clk.left_ms[1],
             clk.to_move == SIDE_WHITE ? 'w' : 'b');
    nus_central_send(line);
}

static void send_new_game(void) {
    char line[48];
    snprintf(line, sizeof line, "N,%s,%lu,%lu\n", clock_mode_name(clk.mode),
             (unsigned long)(clk.base_ms / 1000u), (unsigned long)(clk.increment_ms / 1000u));
    nus_central_send(line);
}

static void on_board_line(const char *line, void *ctx) {
    (void)ctx;
    proto_msg_t m;
    if (!proto_parse(line, &m)) {
        return;
    }
    switch (m.type) {
    case 'S':                          /* game state from the board */
        if (m.n >= 1) {
            ui_set_status(m.field[0]);
        }
        break;
    case 'M':                          /* a move was detected: show it */
        if (m.n >= 1) {
            ui_set_last_move(m.field[0]);
        }
        break;
    case 'P':
        if (m.n >= 3) {
            ui_set_board_battery(m.field[2]);
        }
        break;
    default:
        break;
    }
}

static void on_ble_rx(const uint8_t *data, size_t n, void *ctx) {
    proto_reader_feed(&from_board, data, n, on_board_line, ctx);
}

/* --------------------------------------------------------------- main */

static void apply_preset(void) {
    clock_init(&clk, PRESETS[preset].mode, PRESETS[preset].base_s, PRESETS[preset].inc_s);
    ui_set_preset(PRESETS[preset].label);
    send_new_game();
}

void app_main(void) {
    events = xQueueCreate(16, sizeof(event_t));
    inputs_init();
    buzzer_init();
    ui_init();
    nus_central_start(on_ble_rx, NULL);
    apply_preset();

    uint32_t last = now_ms(), last_sent = last;
    bool in_menu = false;
    for (;;) {
        event_t ev;
        while (xQueueReceive(events, &ev, 0)) {
            uint32_t t = now_ms();
            switch (ev) {
            case EV_WHITE:
            case EV_BLACK: {
                side_t s = ev == EV_WHITE ? SIDE_WHITE : SIDE_BLACK;
                clock_state_t before = clk.state;
                clock_press(&clk, s, t);
                if (clk.state != before || clk.to_move != s) {
                    char line[8];
                    snprintf(line, sizeof line, "T,%c\n", s == SIDE_WHITE ? 'w' : 'b');
                    nus_central_send(line);
                    send_times();
                }
                break;
            }
            case EV_ENC_PUSH:
                if (clk.state == CLK_IDLE || clk.state == CLK_FLAG) {
                    in_menu = !in_menu;
                    if (!in_menu) {
                        apply_preset();
                    }
                } else {
                    clock_pause_toggle(&clk, t);
                }
                break;
            case EV_ENC_CW:
            case EV_ENC_CCW:
                if (in_menu) {
                    int n = (int)(sizeof PRESETS / sizeof PRESETS[0]);
                    preset = (preset + (ev == EV_ENC_CW ? 1 : n - 1)) % n;
                    ui_set_preset(PRESETS[preset].label);
                }
                break;
            }
        }
        uint32_t t = now_ms();
        if (clock_tick(&clk, t - last, t)) {
            beep(clk.state == CLK_FLAG ? 3 : 1);
            if (clk.state == CLK_FLAG) {
                char line[16];
                snprintf(line, sizeof line, "R,%c,flag\n", clk.flagged == SIDE_WHITE ? 'w' : 'b');
                nus_central_send(line);
            }
        }
        last = t;
        if (t - last_sent >= 1000 && clk.state == CLK_RUNNING) {
            send_times();
            last_sent = t;
        }
        ui_render(&clk, in_menu, nus_central_connected());
        vTaskDelay(pdMS_TO_TICKS(50));
    }
    (void)TAG;
}
